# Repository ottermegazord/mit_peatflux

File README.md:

# peatflux-code

Welcome to the peatflux-code!

# Add gpio-poweroff signal for TPL5110
Step 1: Edit config.txt
`sudo nano /boot/config.txt`
Step 2: Add gpio-poweroff overlay at bottom of config.txt, where xx is DONE pin
`dtoverlay=gpio-poweroff,gpiopin= xx`

# Running a script as a service in Raspbian Jessie #

Step 1: Define the service definition to run your script (e.g. yourscript.py)
`cd /lib/systemd/system`
`sudo nano yourscript.service`

Step 2: Create a service definition
Type these out in your _yourscript.service_ service definition
`[Unit]`
`Description=This is my script`
`After=multi-user.target`

`[Service]`
`Type=simple`
`ExecStart=/usr/bin/python /home/pi/yourscript.py`
`Restart=on-abort`

`[Install]`
`WantedBy=multi-user.target`

Essentially, this code means that whenever service is stopped, it will be restarted automatically.

Step 4: Activate your service
`sudo chmod 644 /lib/systemd/system/yourscript.service`
`chmod +x /home/pi/yourscript.py`
`sudo systemctl daemon-reload`
`sudo systemctl enable yourscript.service`
`sudo systemctl start yourscript.service`

Step 4: Check for status of your service
`sudo systemctl status hello.service`

This command will show the status (active/inactive) of your service, and the last instructions and/or returns

Step 5: Restart your RPi and enjoy!

To stop the script we can enter the command
`sudo service yourscript stop`

# Persistent USB Device #

If you have multiple USB devices connected, it could happen that after a reboot the device order is changed (ttyUSB0 is ttyUSB1, or the other way around)

The good news is, that there is a solution for this:

=Find ID's of USB device=
Make sure all the usb devices are plugged in.

Run the following command:
sudo lsusb -v | more
and write down the:

 *idVendor
 *idProduct
 *iSerial

(you can press the spacebar to scroll down)

= Examples =
The FTDI cable used to connect to the Licor 7000 is reported as:
  
  idVendor           0x0403 Future Technology Devices International, Ltd
  idProduct          0x6001 FT232 USB-Serial (UART) IC
  bcdDevice            6.00
  iManufacturer           1 FTDI
  iProduct                2 UT232R
  iSerial                 3 FTWD9PPQ

The FTDI cable used to connect to the Licor 840 is reported as:

  idVendor           0x0403 Future Technology Devices International, Ltd
  idProduct          0x6001 FT232 USB-Serial (UART) IC
  bcdDevice            6.00
  iManufacturer           1 FTDI
  iProduct                2 UT232R
  iSerial                 3 FTYNX3XV

You need the part behind the '0x'. So you don't write down '0x0403' but '0403'.

=Creating rules file=
Create a rules file, with the following example content:

sudo nano /etc/udev/rules.d/99-usb-serial.rules

===Examples ===

GE50A USB

`SUBSYSTEM=="tty", ATTRS{idVendor}=="0403", ATTRS{idProduct}=="6001", ATTRS{serial}=="FTZ1T3BU", SYMLINK+="ttyUSB-ge50a"`

LI7000 USB

`SUBSYSTEM=="tty", ATTRS{idVendor}=="0403", ATTRS{idProduct}=="6001", ATTRS{serial}=="FTYNX3XV", SYMLINK+="li7000"`

LI840 USB

`SUBSYSTEM=="tty", ATTRS{idVendor}=="0403", ATTRS{idProduct}=="6001", ATTRS{serial}=="FTWD9PPQ", SYMLINK+="li840"`

(Put in the values you've written down between the quotes (e.g. replace '0403' with the idVendor of your USB device).

Some devices don't show a serial, for examples like this usb

Aeon ZWave USB stick is reported as:

  idVendor           0x10c4 Cygnal Integrated Products, Inc.
  idProduct          0xea60 CP210x UART Bridge / myAVR mySmartUSB light
  
you can remove that part in the file, so it looks like this:

<code>SUBSYSTEM=="tty", ATTRS{idVendor}=="1a86", ATTRS{idProduct}=="7523", SYMLINK+="ttyUSB-RFX433"</code>

Names should be ttyUSB-UNIQUENAME so you can easily identify them within Domoticz.

=== AeoTec Z-Stick ===
Gen2:
<code>SUBSYSTEM=="tty", ATTRS{idVendor}=="10c4", ATTRS{idProduct}=="ea60", SYMLINK+="ttyUSB-ZStick-2G" </code>

Gen5:
<code>SUBSYSTEM=="tty", ATTRS{idVendor}=="0658", ATTRS{idProduct}=="0200", SYMLINK+="ttyUSB-ZStick-5G"</code>

=When you see no device=
 sudo mknod /dev/ttyUSB0 c 188 0
 sudo mknod /dev/ttyUSB1 c 188 1
And do the steps again.

=Restart and check results=
Restart (sudo reboot) with<br>
<code>sudo shutdown -r now</code><br>
After the reboot you should have two new serial ports (ttyUSB21,ttyUSB22), and they will always be assigned to the devices you have configured in the rules file.<br>

To use the new ports, in Domoticz go to the Setup -> Hardware webpage, highlight the RFXtrx433, and in the Serial Port dropdown list select the new Port 'ttyUSB21'. <br>
Then save.<br>
<br>
Alternatively, you can reload the udev rules without rebooting by running the following command:<br>
<code>sudo  udevadm control --reload</code><br>
Then disconnect and reconnect the USB device, to see if it works.

= Alternative filtering =
When there is a situation that there are more devices with for example the same vendor and product and have no serial number, you can use the command below to add some other filtering.
<code>
udevadm info -a -n /dev/ttyUSBX
</code>

Udevadm info starts with the device specified by the devpath and then walks up the chain of parent devices. It prints for every device found, all possible attributes in the udev rules key format. A rule to match, can be composed by the attributes of the device and the attributes from one single parent device.

Now compare the output of both devices and find some non-sumularities and add it to the 99-usb-serial.rules file

An example is to use the de devpath. The devpath is the number of the bus and port, for example ATTRS{devpath}=="3.1". To make this levels more visual you can use
<code>
lsusb -t
</code>
This gives an example output of

/:  Bus 02.Port 1: Dev 1, Class=root_hub, Driver=ehci_hcd/5p, 480M
    |__ Port 3: Dev 2, If 0, Class=hub, Driver=hub/4p, 480M
        |__ Port 1: Dev 7, If 0, Class=vend., Driver=pl2303, 12M

# Raspberry Pi Set up for Profile Node:<br> #
Step 1: Download Raspbian Jessie image from https://www.raspberrypi.org/downloads/raspbian/ <br>
Step 2: Write Raspbian Jessie image into SD card using Win32DiskImager <br>
Step 3: Plug in Raspberry Pi (with SD card) and switch on connecting it to a LCD Screen <br>
Step 4: Run `sudo apt-get update` and `sudo apt-get dist-upgrade`<br>
Step 5: Download the repository via `git clone git@github.com:alex-cobb/peatflux-code.git`.<br>
Step 5: Enable SSH, SPI and I2C in sudo raspi-config or from the desktop interface Raspberry Configuration.<br>
Step 6: To install the latest version of python software `sudo apt-get install python-dev`<br>
Step 7: Download/transfer the SPI-Py Repository `git clone https://github.com/lthiery/SPI-Py.git`<br>
Step 8: Run `sudo python setup.py build` to build and `sudo python setup.py install` to install the SPI-Py repository. <br>
Step 9: Type `sudo nano /boot/cmdline.txt` and add ip=192.168.0.X at the end of the line. <br>
*note: Add any desired statics IP that you want. <br>

# Passwordless SSH and SCP<br> #
Step 1: Run `ssh-keygen –t rsa`<br>
	Just “Enter” at “Enter passphrase” & “Enter same passphrase again”<br>
Step 2: Run `ssh pi@IPaddress mkdir –p .ssh` to create .ssh directory.<br>
Step 3: Run ` cat .ssh/id_rsa.pub | ssh pi@IPaddresss ‘cat >> .ssh/authorized_keys’`<br>
	Enter pi@IPaddress password (upload generated public keys to designation IP address)<br>
Step 4: Run `ssh pi@IPaddress “chmod 700 .ssh; chmod 640 .ssh/authorized_keys”` (Set Permission)<br>
Step 5: Run `ssh pi@IPaddress` (login server without password)<br>
*Note: Step 1 should not be repeated for master node because id_rsa.pub will already be generated when syncing with the first node. <br>

# DS18B20<br> #
To use the DS18B20 temperature sensor, following steps must be done. <br>
Step 1: Type `sudo nano /boot/config.txt`, scroll to the bottom and add “dtoverlay=w1-gpio”. Once done reboot `sudo reboot`<br>
Step 2: Run `sudo modprobe w1-gpio` and `sudo modprobe w1-therm`. Once done, open the device directory `cd /sys/bus/w1/devices`.<br>
Step 3: List out the directory in devices using `ls` and look for a directory starting with “28- <br>
Step 4: Open the “28- “ directory and type `cat w1-slave`.<br>
Step 5: Run ds18b20.py program `sudo python ds18b20.py` to check if the temperature sensor is working. <br>

# Set RTC Time<br> #
Step 1: Type `sudo nano /boot/config.txt` and add “dtoverlay=i2c-etc,ds1307” at the bottom of the script. Save it and reboot. `sudo reboot`<br>
Step 2: Run `sudo i2cdetect –y 1` to see if the UU shows up where 0x68 should be. <br>
Step 3: Disable the fake hwclock as it will interferes with the real hwclock. `sudo apt-get –y remove fake-hwclock` and `sudo update-rc.d –f fake-hwclock remove`<br>
Step 4: Run `sudo nano /lib/udev/hwclock-set` and comment out these three lines:<br>
	#if [ -e /run/systemd/system ]; then<br>
	# exit 0	<br>
	#fi<br>
Step 5: Check the time of the RTC Pi by using `sudo hwclock –r` or `timedatectl`<br>
Step 6: Run `sudo hwclock –w` to write the internet time to RTC Pi and run `sudo hwclock –r` to check if the time is sync. 
#NTP Client Set up<br>#
Step 1: Run `sudo nano /etc/ntp.conf` and edit the file. Add “tinker panic 0” on top of “driftfile /var/lib/ntp/ntp.drift” and edit the server to “server desired IP address iburst”. <br>
Step 2: Restart NTP on the local machine `sudo service ntp restart`	<br>
Step 3: Test the NTP server `ntpq –c lpeer` and see if there is any responses on the “delay, offset and jitter”<br>

# GPS Hat Set Up for Master Node<br> #
# Prerequisite Settings<br> #
Step 1: Run `sudo raspi-config`, go to Advance Options and disable serial shell (optional) and reboot `sudo reboot`.<br>
Step 2: run update `sudo rpi-update` once done, reboot `sudo reboot`.<br>
Step 3: Install `sudo apt-get install pps-tools`, `sudo apt-get install libcap-dev`, `sudo apt-get install libssl-dev` (may not need this) and `sudo dpkg-reconfigure tzdata` (unless you want all times in UTC) <br>
Step 4: Run `sudo nano /boot/config.txt’ and add “dtoverlay=pps-gpio, gpiopin=18. Save and close. <br>
Step 5: Run `sudo nano /etc/modules` and add “pps-gpio” at the bottom of the script. <br>
Step 6: Run `lsmod | grep pps` and the output should be “pps_gpio 2539 1 pps_core 7943 2 pps_gpio”<br>

# Verifying PPS is working<br> #
Step 1: Run `dmesg | grep pps` <br>
Output should be similar to: <br>
[ 0.000000] Kernel command line: dma.dmachans=0x7f35 bcm2708_fb.fbwidth=656 bcm2708_fb.fbheight=416 bcm2708.boardrev=0x10 bcm2708.serial=0x1a25ea38 smsc95xx.macaddr=B8:27:EB:25:EA:38 bcm2708_fb.fbswap=1 bcm2708.disk_led_gpio=47 bcm2708.disk_led_active_low=0 sdhci-bcm2708.emmc_clock_freq=250000000 vc_mem.mem_base=0x1ec00000 vc_mem.mem_size=0x20000000 dwc_otg.lpm_enable=0 console=tty1 root=/dev/mmcblk0p2 rootfstype=ext4 elevator=deadline rootwait<br>
[ 0.029423] bcm2708: GPIO 18 setup as pps-gpio device<br>
[ 10.159940] pps_core: LinuxPPS API ver. 1 registered<br>
[ 10.161448] pps_core: Software ver. 5.3.6 - Copyright 2005-2007 Rodolfo Giometti <giometti@linux.it><br>
[ 10.172015] pps pps0: new PPS source pps-gpio.18<br>
[ 10.173557] pps pps0: Registered IRQ 188 as PPS source <br>
Step 2: Run `sudo ppstest /dev/pps0`<br>
Output should be similar to: <br>
trying PPS source "/dev/pps0"<br>
found PPS source "/dev/pps0"<br>
ok, found 1 source(s), now start fetching data... <br>
source 0 - assert 1418933982.9980424, sequence: 970 - clear 0.0000000, sequence: 0<br>
source 0 - assert 1418933983.9980454, sequence: 971 - clear 0.0000000, sequence: 0<br>
(Press CTRL+C to quit).<br>
*Note: This indicates the PPS module is loaded(dmesg) and is working (ppstest)<br>

#Enabling PPS/ATOM support in NTPD<br>#
Step 1: Make sure your Raspberry Pi is connected with wifi. <br>
Step 2: Run `wget http://archive.ntp.org/ntp4/ntp-4.2/ntp-4.2.8p6.tar.gz`<br>
	         `tar zxvf ntp-4.2.8p6.tar.gz`<br>
	         `cd ntp-4.2.8p6`<br>
	         `./configure`<br>
	         `make`<br>
                 `sudo make install`<br>
	         `sudo service ntp stop`<br>
	         `sudo cp /usr/local/bin/ntp* /usr/bin/ && sudo cp /usr/local/sbin/ntp* /usr/sbin/<br>
	      
Step 3: Edit the file in `sudo nano /etc/ntp.conf` and add the lines “server 127.127.22.0 minpoll 4 maxpoll 4” and “fudge 127.127.22.0”<br>
Step 4: Amend the line to add the word “prefer” (server 0.debian.pool.ntp.org iburst prefer) Save and close once done. <br>
Step 5: Restart the NTP server using `sudo service ntp restart`<br>
Step 6: Run `ntpq –pn` to check if the data is receiving. <br>

# Getting the time stand-alone<br> #
Step 1: Disable Serial Shell go to `sudo raspi-config` -> Advance Option and disable Serial Shell (optional)<br>
Step 2: Reboot Raspberry Pi `sudo reboot`<br>
Step 3: Install minicom `sudo apt-get install minicom`<br>
Step 4: Run `minicom –b 9600 –o –D /dev/ttyAMA0` (Ctrl –A to exit minicom)<br>
Step 5: Disable tty using:<br>
	`sudo systemctl1 stop serial-getty@ttyS0.service`<br>
	`sudo systemctl1 disable seria-getty@ttys0.service`<br>
Step 6: Reboot the system `sudo shutdown –r now`<br>
Step 7: Install GPSD `sudo apt-get install gpsd gpsd-clients python-gps<br>
Step 8: Disable GPSD socket:<br>
	`sudo systemctl stop gpsd.socket`<br>
	`sudo systemctl disable gpsd.socket`<br>
Step 9: Edit the gpsd file `sudo nano /etc/default/gpsd` into <br>
`#Default settings for gpsd.`<br>
`#Please do not edit this file directly – use ‘dpkg-reconfigure gpsd’ to `<br>
`#change the options.`<br>
START_DAEMON=”true”<br>
GPSD_OPTIONS=”-n”<br>
DEVICES=”/dev/ttyS0”<br>
USBAUTO=”false”<br>
GPSD_SOCKET=”var/run/gpsd.sock”<br>
Step 10: Reboot again `sudo reboot`<br>

# Raspberry Pi 3 UART & Bluetooth complications<br> #
Step 1: Make sure your Raspberry Pi is on the latest update. Run `sudo apt-get update`, `sudo apt-get upgrade`, `sudo apt-get dist-upgrade` and `sudo rpi-update`. To check if there is any updates. <br>
Step 2: Edit config.txt file `sudo nano /boot/config.txt` and add 2 lines at the endof the file. <br>
	`#Allow the normal UART pins to work`<br>
	`dtoverlay=pi3-disable-bt-overlay`<br>
Step 3: Stop the Bluetooth modem from trying to use the UART<br>
	`sudo systemctl disable hciuart`<br>
Step 4: If you have “smsc95xx.turbo_mode=N in your /boot/cmdline.txt, remove it. <br>

# GPSD Software <br> #
Step 1: Install GPSD software `sudo apt-get install gpsd gpsd-clients python-gps<br>
Step 2: If there is error, re-run `sudo apt-get update` and `sudo apt-get upgrade`.<br>
Step 3: Try and start the gpsd service temporarily `sudo gpsd /dev/ttyAMA0 –n –F /var/run/gpsd.sock`<br>
Step 4: run `cgps –s` and there should be an output. <br>

# Configuring gpsd to auto-start<br> #
Step 1: Run `sudo nano /etc/default/gpsd` and edit the file to GPSD_OPTIONS=”-n”, USBAUTO=”false” and DEVICE=”/dev/ttyAMA0”.<br>
Step 2: If GPSD did not auto-start, run `sudo ln –s /lib/system/system/gpsd.service /etc/systemd/system/multi=user.targer.wants/<br>

# Raspbian Jessie system service fix <br> # 
To disable gpsd system service run `sudo systemctl stop gpsd.socket` and `sudo systemctl disable gpsd.socket`<br>

# Changes to your NTP configuration #
Edit the file in `sudo nano /etc/ntp.conf` and change/add in these lines:<br>
	#Kernel-mode PPS reference-clock for the precise seconds<br>
	server 127.127.22.0 minpoll 4 maxpoll 4<br>
	fudge 127.127.22.0 refid kPPS<br>

	#Coarse time reference-clock – nearest second<br>
	server 127.127.28.0. minpoll 4 maxpoll 4 iburst prefer<br>
	fudge 127.127.28.0. time1 +0.105 flag1 1 refid GPSD stratum 1<br>
Save and reboot after done. <br>

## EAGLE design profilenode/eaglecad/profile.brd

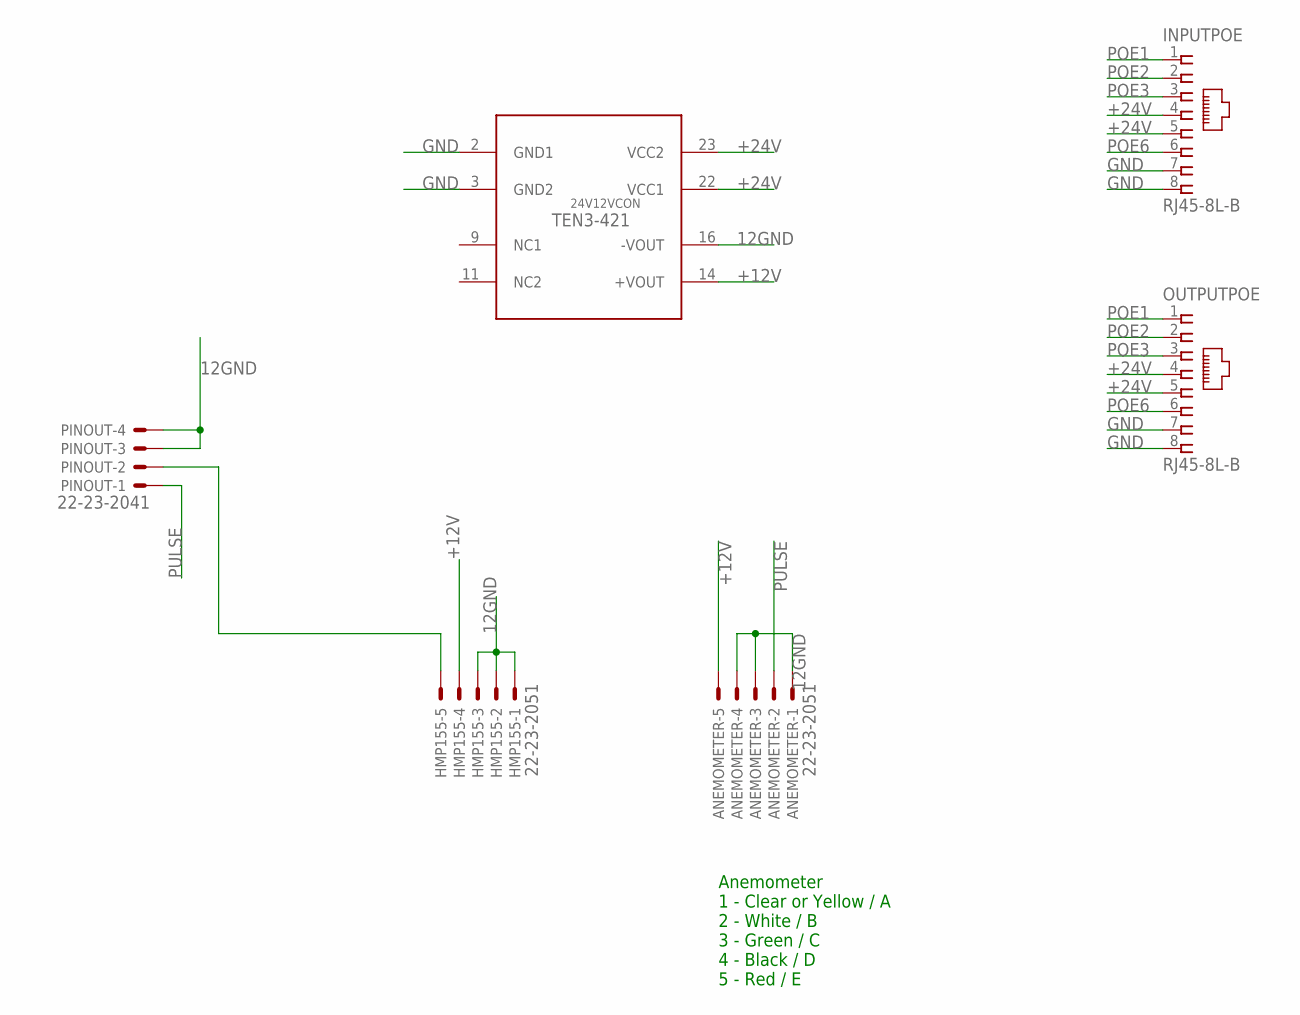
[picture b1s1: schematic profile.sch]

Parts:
24V12VCON: TEN3-421; SOCKET-24-6
ANEMOMETER: 22-23-2051
HMP155: 22-23-2051
INPUTPOE: RJ45-8L-B; RJ45-NO-SHIELD
OUTPUTPOE: RJ45-8L-B; RJ45-NO-SHIELD
PINOUT: 22-23-2041

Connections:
12GND: 24V12VCON.16 (-VOUT), ANEMOMETER.1, ANEMOMETER.3, ANEMOMETER.4, HMP155.1, HMP155.2, HMP155.3, PINOUT.3, PINOUT.4
+12V: 24V12VCON.14 (+VOUT), ANEMOMETER.5, HMP155.4
+24V: 24V12VCON.22 (VCC1), 24V12VCON.23 (VCC2), INPUTPOE.4, INPUTPOE.5, OUTPUTPOE.4, OUTPUTPOE.5
GND: 24V12VCON.2 (GND1), 24V12VCON.3 (GND2), INPUTPOE.7, INPUTPOE.8, OUTPUTPOE.7, OUTPUTPOE.8
unnamed: HMP155.5, PINOUT.2
POE1: INPUTPOE.1, OUTPUTPOE.1
POE2: INPUTPOE.2, OUTPUTPOE.2
POE3: INPUTPOE.3, OUTPUTPOE.3
POE6: INPUTPOE.6, OUTPUTPOE.6
PULSE: ANEMOMETER.2, PINOUT.1

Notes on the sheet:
Anemometer 1 - Clear or Yellow / A 2 - White / B 3 - Green / C 4 - Black / D 5 - Red / E

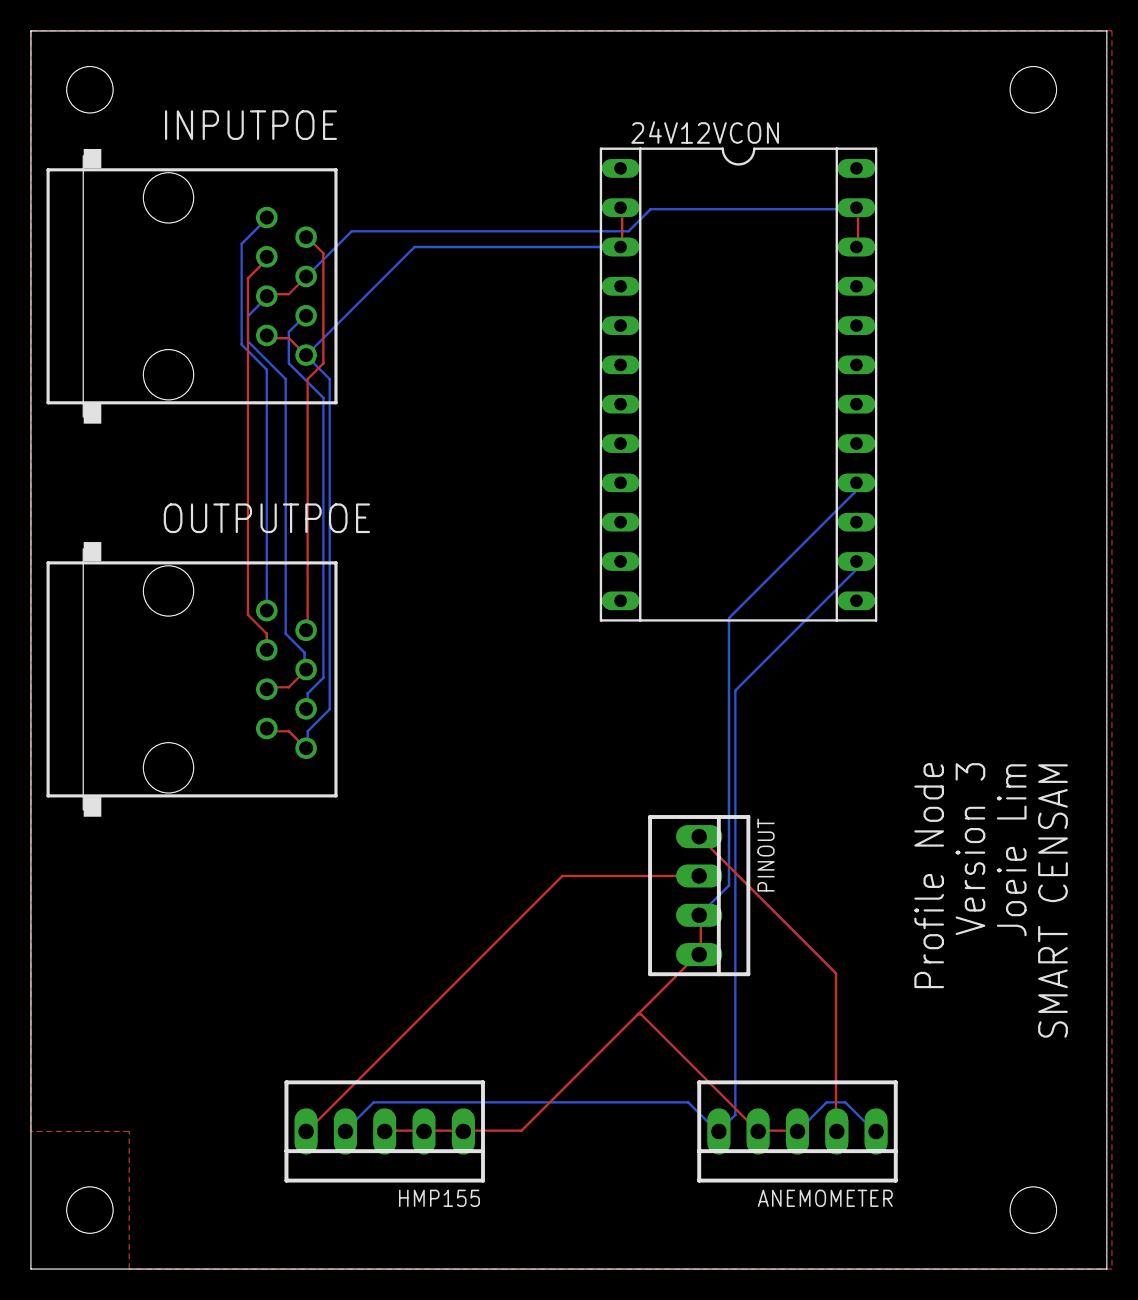
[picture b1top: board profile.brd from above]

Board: 2 copper layers, 69.5 x 80.0 mm, 6 parts (0 on the bottom side), 10 nets.

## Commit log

2016-10-11 Adds Li-7000 Python Repo: Basic functions and instructions to talk to and calibrate the Li-7000
2016-10-11 remove test file: test1.py
2016-10-11 Adds Valve Control Program to peatflux-code. Needs to streamline and modularize functions, see Issues
2016-10-12 Add Schematics for Relays
2016-10-12 Adds PID controller program
2016-10-12 Adds li840.py - module to communicate with li840, adds time tag to datastream
2016-10-12 Adds updated class_li840.py: Repository to communicate with Li840. Also adds time
2016-10-13 Adds NTP Network Time installation instructions for RPi
2016-10-14 Adds routine that will calibrate every 10th minute for testing
2016-10-14 Adds 10Hz log and schdeduled calibration example, updated class_li7000.py for datastream bugs
2016-10-14 adds wiring schematic for PID controller
2016-10-17 Adds service instructions for peatflux-code/li7000. See Github for daemon activation instructions
2016-10-17 Updates README.md with "How to run your script as a service" instructions
2016-10-17 Adds a module to control pneumatic valves
2016-10-17 Adds a class to control valves
2016-10-19 Adds logging during calibration
2016-10-19 Adds polling to calibration process, does not log
2016-10-19 Adds logging during calibration, streamlined logging algo
2016-10-19 Adds logging during calibration, streamlined logging algo v2
2016-10-19 Updates to logging algo for calibration
2016-10-19 Adds open valve channel in class_valve.py
2016-10-19 Set pin numbering mode on class_valve.py
2016-10-19 updated open relay function on class_valve.py
2016-10-19 Adds close valve function to class_valve.py
2016-10-19 Creates a master eddy covariance program
2016-10-19 Integrate class_li7000.py with valve.py
2016-10-19 Adds an EC program that calibrates LI7000 by the hour
2016-10-20 Add valve control routine to eddy covariance system
2016-10-20 Adds multiple calibration process for calibration function in class_li7000.py
2016-10-20 Fixed bug in calibration algo
2016-10-24 Creates Li840_EC.py, reads from LI840 without valve control
2016-10-24 Adds multiple li840 readings from profile nodes
2016-10-24 Adds multiple li840 readings from profile nodes v2
2016-10-24 Updates Li840_EC routine
2016-10-24 Adds valve control to li840_ec.py
2016-10-24 Adds valve control, runs every 10 minutes, to li840_ec.py
2016-10-24 li840_EC.py now runs every 10 minutes
2016-10-25 New algorithm for reading gas at 8 nodes
2016-10-25 Adds calibration function to class_li840
2016-10-27 Creates profile node log directory
2016-10-27 Test file:megadeth.py
2016-10-27 test file megadeth.py
2016-10-27 Adds arguments to li840 class
2016-10-27 Fixes li840_calibration error
2016-10-27 Adds calibration at 2330hrs for li840_EC.py
2016-10-27 Adds persistent USB for li840 and li7000
2016-10-27 Adds "Persistent USB Device" Instructions
2017-01-11 Adds sungrow-0.1b7 to peatflux-code
    Includes porting instructions to Raspberry Pi
2017-01-13 Test file test
2017-01-18 Add files via upload
    Items needed for profile node
2017-01-19 Fixes scheduling bug in li840_ec.py
2017-01-20 Add files via upload
    Adds documentation to eddy_covariance repository
2017-01-20 Profile node breakout board
2017-01-23 Add files via upload
    Inventory list for profile node
2017-01-23 Complete discharge of gas from M100B takes about ~3 seconds => Interval between calibrations increased to 5 seconds
2017-01-23 Add files via upload
    Component list for Profile node PCB board
2017-01-23 Adds test file => megadeth.py (delete after use)
2017-01-23 Add files via upload
    Pin connection schematic for air flow controller M100B
2017-01-23 Revert "Repo joeielim"
2017-01-23 finalized li7000 calibration routine
2017-01-23 Remove profilenode folder
2017-01-23 re-adding profilenode folder with catergories.
2017-01-23 Add files via upload
    pin connection schematic for MKS1579A
2017-01-23 Remove profilenode
2017-01-23 Adding profilenode folder
2017-01-24 Adding py-max31865 main file
2017-01-24 Adds xml to csv conversion to directory
2017-01-24 fixes timing issues in LI840_EC.py routine
2017-01-24 fixes subroutine for li840 v3
2017-01-24 Remove item list and component item pcb
2017-01-24 Re-adding item list.
2017-01-25 Removing item_list.docx and re-adding to profilenode folder
2017-01-25 Re-adding item_list.docx into profilenode folder.
    Creating a new folder called "Hardware" for item_list.docx
2017-01-26 Updates Li-840 and Li-7000 calibration and profile reading routine
2017-01-31 Added Datasheet and inkscape design
    Data sheet for Gill 3 Cup Anemometer and HMP155.
    Inkscape design of the overall layout of profile node in flow chart and profile node breakout board.
2017-02-01 Revert "Added Datasheet and inkscape design"
    This reverts commit c1f688d3fc476dafb39650433fd8f485ca8cb59c.
2017-02-01 Removing item_list.docx and re-adding it
2017-02-01 Re-adding item_list.docx
2017-02-01 Added Datasheet and Inkscape design
2017-02-06 Remove item-list.docx
2017-02-06 updated item_list.docx
2017-02-06 Add files via upload
    updated closed path circuit schematic
2017-02-07 file log to external disk
2017-02-07 remove item_list.docx
2017-02-07 Re-addng item_list.docx
2017-02-10 file is complete with the header input for log txt
2017-02-17 Adding SPI-Pi-master library
2017-02-17 updated with header
2017-02-17 remove header file
2017-02-20 Removing item_list.docx
2017-02-22 Remove py-max31865.zip
2017-02-22 Upload ABElectronics_Python_Libraries
2017-02-22 Upload py-max31865
2017-02-22 upload profile.txt
2017-02-22 Upload item_list.docx
2017-02-22 Steps to set up profile node
2017-02-22 Upload HMP155 User Guide
2017-02-27 Update li840.py, removed redundant repositories
2017-02-27 Adds GE50A module to repository
2017-02-28 adds logging routine for ge50a mass flow controller
2017-02-28 adds ge50a routine to peatflux-code repo
2017-02-28 adds /usr/bin/python to ge50a routine
2017-02-28 Add PID program to peatflux-code
2017-03-01 Upload passwordless ssh and scp steps
2017-03-01 Remove item_list
2017-03-01 upload updated item_list.docx
2017-03-02 schematic MKS GE50A
2017-03-02 reupload profile.py
2017-03-02 Reformatted profile.py code
2017-03-02 upload enclosure layout and LiFePO4wered guide
2017-03-02 Upload LiFePO4wered repository
2017-03-07 DS18B20 Program
2017-03-20 Upload windtunnel Arduino Program
2017-03-21 Upload pwn fan controller layout
2017-03-21 Upload PWM Layout
2017-03-21 adds 3way valve routine
2017-03-29 Remove enclosure layout
2017-03-29 Upload updated enclosure layout
2017-03-30 Updates pid.py
2017-03-31 adds three way valve and v5 v6 valves to eddy_covariance.py
2017-03-31 adds V6 and V5 valves to eddy covariance programs
2017-03-31 reformat indentation
2017-05-22 Adrian Profile Node Layout
2017-05-25 Updated profilenode connections
2017-06-15 TPL5110 functionality
    Adds instructions to delete LiFePO4wered, adds gpio-power
2017-07-05 Add in profile node and master node manual
2017-10-17 add analog input (in celsius) method to pywatlow directory
2017-10-17 adds get_set_point and get_heat_power methods to pywatlow
2017-10-21 adds datetime parameter to pywatlow.py
2017-10-21 Adds sample CSV
